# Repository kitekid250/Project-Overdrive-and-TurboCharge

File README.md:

# Project Overdrive and TurboCharge

OverDrive and TurboCharge are simple motor control modules designed for use by the Bucknell Department of Mechanical Engineering.  The boards are designed to be a simple interface with motors and encoders.  ProjectOverdrive is the big brother of Turbocharger and was develped to handle 6 high power motors (24V @ 20A ea) and have 6 encoder counters designed for an Arduino Due. Project TurboCharge is the little brother, powered from a L298P dual H-bridge, and fits nicely on top of an Arduino Uno.  It has two channels of encoder counting using the same chip as its big brother.  Its signficantly cheaper than the TurboCharge, making it the ideal candidate for projects requiring smaller motors.

###Documentation
You should read the docs corresponding to your board then follow the Installation/QuickStart instructions below

The documentation for the OverDrive Board is [here](https://github.com/kitekid250/Project-Overdrive-and-TurboCharge/blob/master/Documentation/OverDrive%20Documentation.md).

The documentation for the TurboCharge Board is [here](https://github.com/kitekid250/Project-Overdrive-and-TurboCharge/blob/master/Documentation/TurboCharge%20Documentation.md).

The (advanced) documentation for the encoder counter IC's is [here](https://github.com/kitekid250/Project-Overdrive-and-TurboCharge/blob/master/Documentation/LS7366R%20Encoder%20Counter%20Documentation.md).

###Installation/QuickStart
Here are the steps to get going, starting from square one.

1. Install Arduino 1.6.6 from [here](https://www.arduino.cc/en/Main/OldSoftwareReleases#previous).  There is a good chance that other Arduino versions will work, but this library is confirmed to work on 1.6.6.
2. Download the [OverDrive library](https://github.com/kitekid250/Project-Overdrive-and-TurboCharge/raw/master/OverDrive/OverDrive_Library.zip) if you have an OverDrive board or the [TurboCharge library](https://github.com/kitekid250/Project-Overdrive-and-TurboCharge/raw/master/TurboCharge/TurboCharge_Library.zip) if you have a TurboCharge board.  Keep them as .ZIP files so Arduino can easily import them.
3. Install the library you just downloaded by navigating to Sketch->Include Library-> Add .ZIP Library
4. In the Arduino IDE navigate to Tools->Board->Boards Manager
5. Search for "due" and install version 1.6.6 of the one board that comes up.
6. Navigate to File->Examples->[OverDrive/TurboCharge]_Library->Example->E01...
7. Connect the Arduino Due or Arduino Uno that is connected to your OverDrive or TurboCharge board respectively.  If it is a Due, make sure that you plug into the Due's Programming Port (it says it on the bottom of the board).
8. Select the correct COM port from Tools->Port->[Whichever indicates "(Arduino Due/Uno)"]
9. Select Tools->Board->[Arduino Due (Programming Port) / Arduino Uno]
10. Press the Upload (right arrow) button in the toolbar to run the example on the board.

###About
This project is currently maintained by Ward Prescott (erp006@bucknell.edu), however Phil Diefenderfer is responsible for the current hardware design and the first draft of the documentation and libraries.

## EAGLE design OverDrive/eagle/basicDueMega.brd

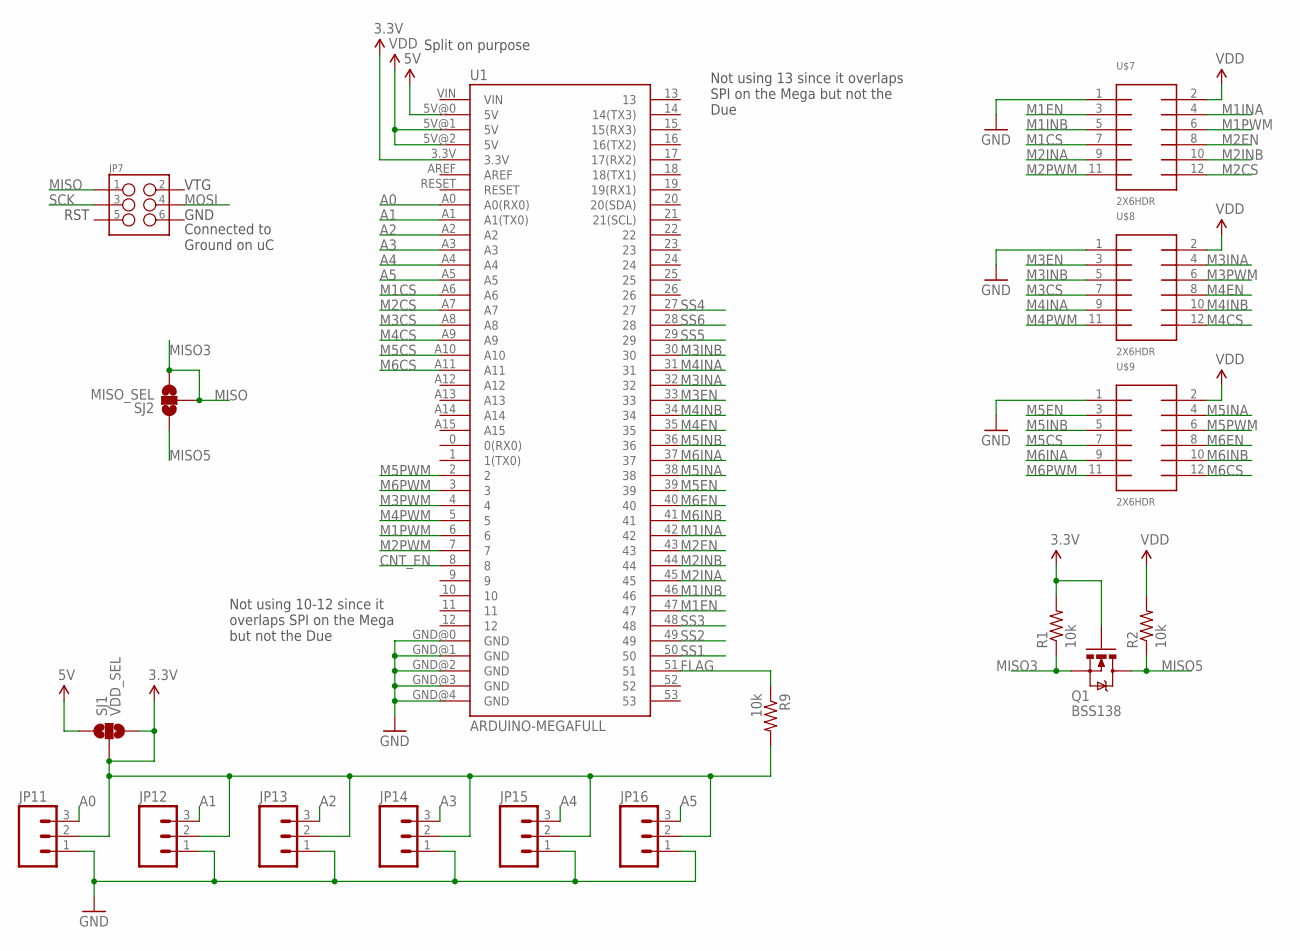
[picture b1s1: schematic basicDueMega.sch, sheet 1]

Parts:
JP7: M03X2POGO_PINS; 2X3_POGO
JP11, JP12, JP13, JP14, JP15, JP16: M03LOCK; 1X03_LOCK
Q1: MOSFET-NCHANNELBSS123LT1G; SOT23
R1, R2, R9: 10k; 0603-RES
SJ1: VDD_SEL; SJ_2
SJ2: MISO_SEL; SJ_2
U1: ARDUINO-MEGAFULL; ARDUINO_MEGA
U$7, U$8, U$9: 2X6HDR; 2X6_2MM_SHROUD

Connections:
3.3V: JP11.2, JP12.2, JP13.2, JP14.2, JP15.2, JP16.2, Q1.1 (G), R1.2, R9.2, SJ1.2, SJ1.3, U1.3.3V
5V: SJ1.1, U1.5V@0 (5V); also elsewhere on the board
A0: JP11.3, U1.A0 (A0(RX0))
A1: JP12.3, U1.A1 (A1(TX0))
A2: JP13.3, U1.A2
A3: JP14.3, U1.A3
A4: JP15.3, U1.A4
A5: JP16.3, U1.A5
CNT_EN: U1.8; also elsewhere on the board
FLAG: R9.1, U1.51; also elsewhere on the board
GND: JP11.1, JP12.1, JP13.1, JP14.1, JP15.1, JP16.1, U1.GND@0 (GND), U1.GND@1 (GND), U1.GND@2 (GND), U1.GND@3 (GND), U1.GND@4 (GND), U$7.1, U$8.1, U$9.1; also elsewhere on the board
M1CS: U1.A6, U$7.7
M1EN: U1.47, U$7.3
M1INA: U1.42, U$7.4
M1INB: U1.46, U$7.5
M1PWM: U1.6, U$7.6
M2CS: U1.A7, U$7.12
M2EN: U1.43, U$7.8
M2INA: U1.45, U$7.9
M2INB: U1.44, U$7.10
M2PWM: U1.7, U$7.11
M3CS: U1.A8, U$8.7
M3EN: U1.33, U$8.3
M3INA: U1.32, U$8.4
M3INB: U1.30, U$8.5
M3PWM: U1.4, U$8.6
M4CS: U1.A9, U$8.12
M4EN: U1.35, U$8.8
M4INA: U1.31, U$8.9
M4INB: U1.34, U$8.10
M4PWM: U1.5, U$8.11
M5CS: U1.A10, U$9.7
M5EN: U1.39, U$9.3
M5INA: U1.38, U$9.4
M5INB: U1.36, U$9.5
M5PWM: U1.2, U$9.6
M6CS: U1.A11, U$9.12
M6EN: U1.40, U$9.8
M6INA: U1.37, U$9.9
M6INB: U1.41, U$9.10
M6PWM: U1.3, U$9.11
MISO3: JP7.P$1 (1), Q1.2 (S), R1.1, SJ2.2, SJ2.3
MISO5: Q1.3 (D), R2.1, SJ2.1; also elsewhere on the board
MOSI: JP7.P$4 (4); also elsewhere on the board
SCK: JP7.P$3 (3); also elsewhere on the board
SS1: U1.50; also elsewhere on the board
SS2: U1.49; also elsewhere on the board
SS3: U1.48; also elsewhere on the board
SS4: U1.27; also elsewhere on the board
SS5: U1.29; also elsewhere on the board
SS6: U1.28; also elsewhere on the board
VDD: R2.2, U1.5V@1 (5V), U1.5V@2 (5V), U$7.2, U$8.2, U$9.2

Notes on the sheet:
BSS138
Connected to Ground on uC
VTG
Not using 13 since it overlaps SPI on the Mega but not the Due
Not using 10-12 since it overlaps SPI on the Mega but not the Due
MISO
RST
GND
Split on purpose

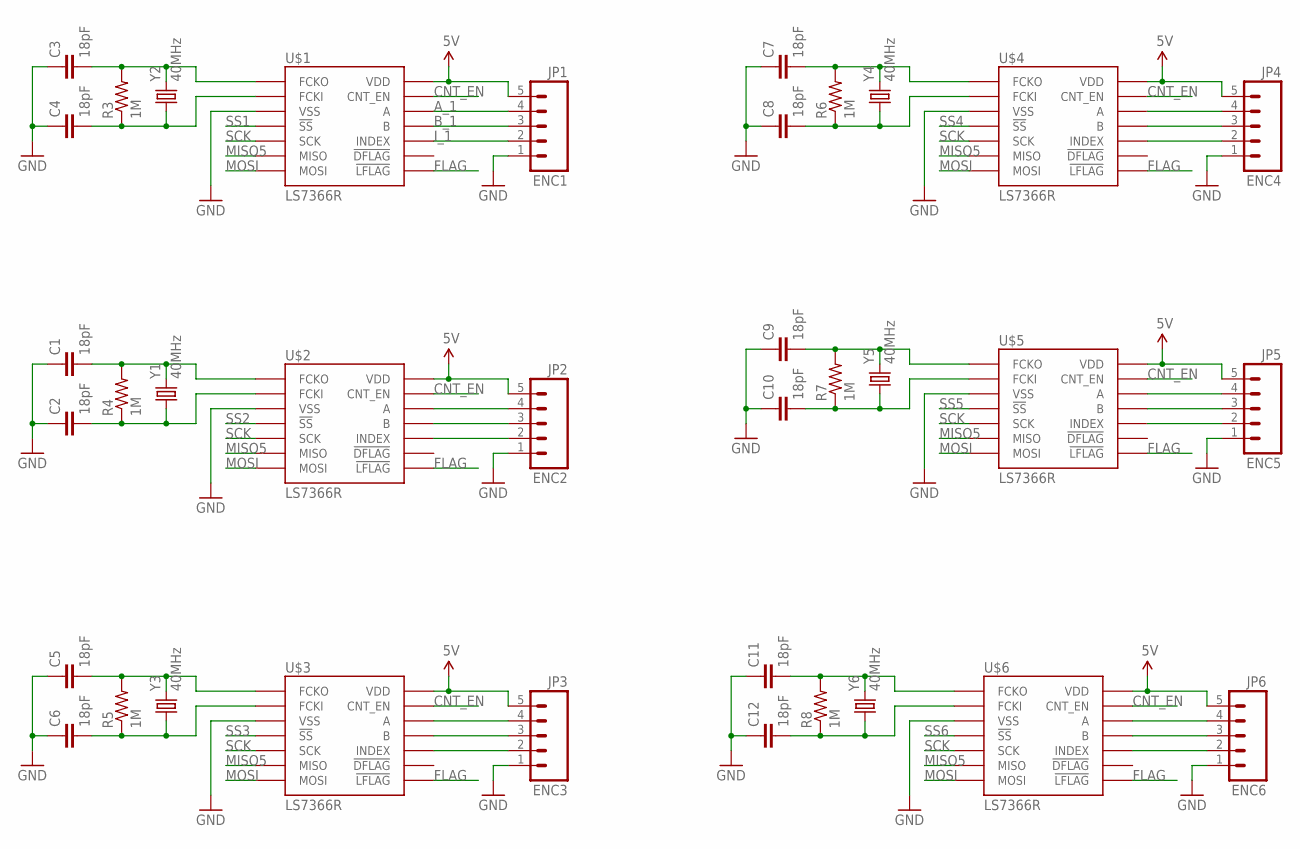
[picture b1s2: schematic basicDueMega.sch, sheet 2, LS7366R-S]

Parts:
C1, C2, C3, C4, C5, C6, C7, C8, C9, C10, C11, C12: 18pF; 0603-CAP
JP1: ENC1; 1X05_LOCK
JP2: ENC2; 1X05_LOCK
JP3: ENC3; 1X05_LOCK
JP4: ENC4; 1X05_LOCK
JP5: ENC5; 1X05_LOCK
JP6: ENC6; 1X05_LOCK
R3, R4, R5, R6, R7, R8: 1M; 0603-RES
U$1, U$2, U$3, U$4, U$5, U$6: LS7366R; SOIC14
Y1, Y2, Y3, Y4, Y5, Y6: 40MHz; CRYSTAL-SMD-5X3

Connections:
5V: JP1.5, JP2.5, JP3.5, JP4.5, JP5.5, JP6.5, U$1.14 (VDD), U$2.14 (VDD), U$3.14 (VDD), U$4.14 (VDD), U$5.14 (VDD), U$6.14 (VDD); also elsewhere on the board
A_1: JP1.4, U$1.12 (A)
B_1: JP1.3, U$1.11 (B)
CNT_EN: U$1.13 (CNT_EN), U$2.13 (CNT_EN), U$3.13 (CNT_EN), U$4.13 (CNT_EN), U$5.13 (CNT_EN), U$6.13 (CNT_EN); also elsewhere on the board
FLAG: U$1.8 (!LFLAG), U$2.8 (!LFLAG), U$3.8 (!LFLAG), U$4.8 (!LFLAG), U$5.8 (!LFLAG), U$6.8 (!LFLAG); also elsewhere on the board
GND: C1.1, C2.1, C3.1, C4.1, C5.1, C6.1, C7.1, C8.1, C9.1, C10.1, C11.1, C12.1, JP1.1, JP2.1, JP3.1, JP4.1, JP5.1, JP6.1, U$1.3 (VSS), U$2.3 (VSS), U$3.3 (VSS), U$4.3 (VSS), U$5.3 (VSS), U$6.3 (VSS); also elsewhere on the board
I_1: JP1.2, U$1.10 (INDEX)
MISO5: U$1.6 (MISO), U$2.6 (MISO), U$3.6 (MISO), U$4.6 (MISO), U$5.6 (MISO), U$6.6 (MISO); also elsewhere on the board
MOSI: U$1.7 (MOSI), U$2.7 (MOSI), U$3.7 (MOSI), U$4.7 (MOSI), U$5.7 (MOSI), U$6.7 (MOSI); also elsewhere on the board
unnamed: C3.2, R3.2, U$1.1 (FCKO), Y2.3 (2)
unnamed: C4.2, R3.1, U$1.2 (FCKI), Y2.1
unnamed: JP2.4, U$2.12 (A)
unnamed: JP2.3, U$2.11 (B)
unnamed: JP2.2, U$2.10 (INDEX)
unnamed: C1.2, R4.2, U$2.1 (FCKO), Y1.3 (2)
unnamed: C2.2, R4.1, U$2.2 (FCKI), Y1.1
unnamed: JP3.4, U$3.12 (A)
unnamed: JP3.3, U$3.11 (B)
unnamed: JP3.2, U$3.10 (INDEX)
unnamed: C5.2, R5.2, U$3.1 (FCKO), Y3.3 (2)
unnamed: C6.2, R5.1, U$3.2 (FCKI), Y3.1
unnamed: JP4.4, U$4.12 (A)
unnamed: JP4.3, U$4.11 (B)
unnamed: JP4.2, U$4.10 (INDEX)
unnamed: C7.2, R6.2, U$4.1 (FCKO), Y4.3 (2)
unnamed: C8.2, R6.1, U$4.2 (FCKI), Y4.1
unnamed: JP5.4, U$5.12 (A)
unnamed: JP5.3, U$5.11 (B)
unnamed: JP5.2, U$5.10 (INDEX)
unnamed: C9.2, R7.2, U$5.1 (FCKO), Y5.3 (2)
unnamed: C10.2, R7.1, U$5.2 (FCKI), Y5.1
unnamed: JP6.4, U$6.12 (A)
unnamed: JP6.3, U$6.11 (B)
unnamed: JP6.2, U$6.10 (INDEX)
unnamed: C11.2, R8.2, U$6.1 (FCKO), Y6.3 (2)
unnamed: C12.2, R8.1, U$6.2 (FCKI), Y6.1
SCK: U$1.5 (SCK), U$2.5 (SCK), U$3.5 (SCK), U$4.5 (SCK), U$5.5 (SCK), U$6.5 (SCK); also elsewhere on the board
SS1: U$1.4 (!SS); also elsewhere on the board
SS2: U$2.4 (!SS); also elsewhere on the board
SS3: U$3.4 (!SS); also elsewhere on the board
SS4: U$4.4 (!SS); also elsewhere on the board
SS5: U$5.4 (!SS); also elsewhere on the board
SS6: U$6.4 (!SS); also elsewhere on the board

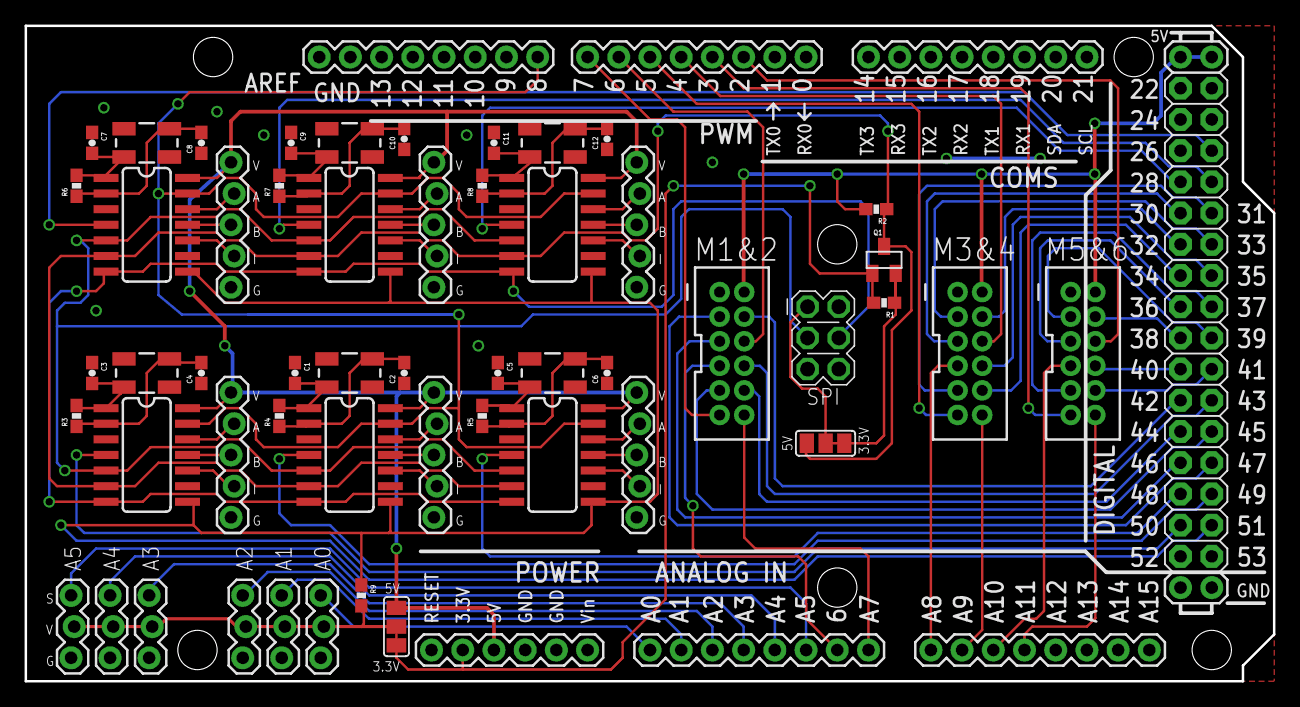
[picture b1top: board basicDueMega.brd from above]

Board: 2 copper layers, 101.6 x 53.3 mm, 53 parts (0 on the bottom side), 82 nets.

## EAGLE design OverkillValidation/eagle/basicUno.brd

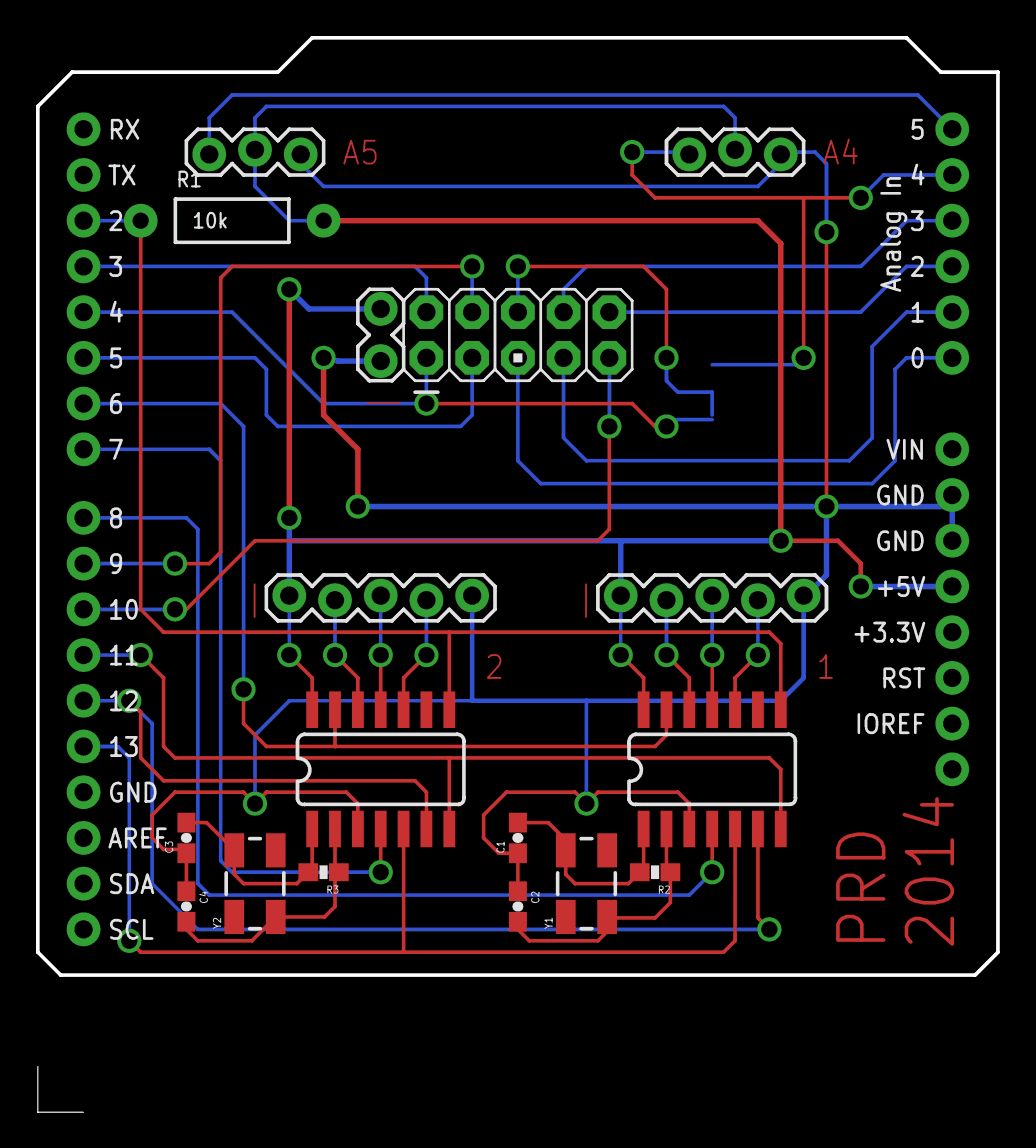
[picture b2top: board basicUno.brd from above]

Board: 2 copper layers, 53.3 x 59.6 mm, 19 parts (1 on the bottom side), 31 nets.

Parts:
C1, C2, C3, C4: 18pF; 0603-CAP
JP1: EN1; 1X05_LOCK
JP2: EN2; 1X05_LOCK
JP3: M05X2PTH; AVR_ICSP
JP4: M02LOCK; 1X02_LOCK
JP5: A4; 1X03_LOCK
JP6: A5; 1X03_LOCK
R1: 10k; AXIAL-0.4
R2, R3: 1M; 0603-RES
SJ1: SJ_2
U$1, U$2: LS7366R; SOIC14
U$3: ARDUINO_R3_SHIELD; UNO_R3_SHIELD
Y1, Y2: 40MHz; CRYSTAL-SMD-5X3

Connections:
5V: JP1.1, JP2.1, JP4.1, JP5.2, JP6.2, R1.P$2, U$1.14, U$2.14, U$3.5V
!FLAG: R1.P$1, U$1.8, U$2.8, U$3.D2
!SS1: U$1.4, U$3.D8
!SS2: U$2.4, U$3.D7
A4: JP5.3, SJ1.3, U$3.A4
A5: JP6.3, U$3.A5
CNT_EN: U$1.13, U$2.13, U$3.D6
GND: C1.1, C2.1, C3.1, C4.1, JP1.5, JP2.5, JP4.2, JP5.1, JP6.1, U$1.3, U$2.3, U$3.GND@0, U$3.GND@1
M1CS: JP3.5, U$3.A0
M1EN: JP3.1, SJ1.1, U$3.D4
M1INA: JP3.2, U$3.D3
M1INB: JP3.3, U$3.D5
M1PWM: JP3.4, U$3.D9
M2CS: JP3.10, U$3.A2
M2EN: JP3.6, SJ1.2
M2INA: JP3.7, U$3.A1
M2INB: JP3.8, U$3.A3
M2PWM: JP3.9, U$3.D10
MISO: U$1.6, U$2.6, U$3.D12
MOSI: U$1.7, U$2.7, U$3.D11
unnamed: JP1.2, U$1.12
unnamed: JP1.3, U$1.11
unnamed: JP1.4, U$1.10
unnamed: JP2.2, U$2.12
unnamed: JP2.3, U$2.11
unnamed: JP2.4, U$2.10
unnamed: C1.2, R2.2, U$1.1, Y1.3
unnamed: C2.2, R2.1, U$1.2, Y1.1
unnamed: C3.2, R3.2, U$2.1, Y2.3
unnamed: C4.2, R3.1, U$2.2, Y2.1
SCK: U$1.5, U$2.5, U$3.D13

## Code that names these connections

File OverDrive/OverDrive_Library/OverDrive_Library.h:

#ifndef _OVERDRIVE_BASIC
#define _OVERDRIVE_BASIC

// Encoder Interface Pins
#define ENC1 50
#define ENC2 49
#define ENC3 48
#define ENC4 27
#define ENC5 29
#define ENC6 28
#define CNT_EN 8
#define FLAG 51
// +SPI on ICSP header

// Driver Interface Pins
#define M1CS A6
#define M2CS A7
#define M3CS A8
#define M4CS A9
#define M5CS A10
#define M6CS A11

#define M1PWM 6
#define M2PWM 7
#define M3PWM 4
#define M4PWM 5
#define M5PWM 2
#define M6PWM 3

#define M1EN 47
#define M1INA 42
#define M1INB 46

#define M2EN 43
#define M2INA 45
#define M2INB 44

#define M3EN 33
#define M3INA 32
#define M3INB 30

#define M4EN 35
#define M4INA 31
#define M4INB 34

#define M5EN 39
#define M5INA 38
#define M5INB 36

#define M6EN 40
#define M6INA 37
#define M6INB 41

// Constants
#define ENABLED 1
#define DISABLED 0
#define FORWARD 0
#define BACKWARD 1

#define MOTOR1 1
#define MOTOR2 2
#define MOTOR3 3
#define MOTOR4 4
#define MOTOR5 5
#define MOTOR6 6

class OverDriveBasic
{
  public:
    OverDriveBasic(int motorNum); 
    void setDirection(int dir);
    void setEnable(int en);
    void setPWM(int spd);
    int getCurrent();
   private:
     int _MOTOR;
     int _EN;
     int _INA;
     int _INB;
     int _PWM;
     int _CS;
};

#endif /* _OVERDRIVE_BASIC */

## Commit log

2015-03-16 Actual first Commit of Files being migrated
    First Commit of Files being migrated from Google Code to GitHub
2015-06-02 Updated Pin Definitions for Production Revision
    The pin defs in the header changed quite a bit.
2015-06-03 Fixed the issue with the SPI library and Arduino Due misbehaving in the LS7366R library. Issue was where SPI.begin() was in the constructor which caused the Due to lock up. This works in the Uno but 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
2015-06-03 Removed OverDriveTesting in the code folder. It is old and really should not be used or present.
2015-06-09 Added Suggestions Text File
    This could serve as a repository for our thoughts on this project, and a
    psuedo To-Do list. We could incorporate git issues as well if desired.
2015-06-09 Added Example and Fixed a Pin
    The example works with the due and a motor. The pin mis-mapped was
    M1_INA.
2015-06-25 Added Set Counter Functionality
    It works, though the user has to make sure not to pass a number that
    exceeds the byte length the counter register is set to.
2015-10-17 Added LS User Guide PDF
    It was only in the Turbo repo though it applies to both Turbo Charge and
    OverDrive
2015-11-09 Started Merge of Two Repos, Started Markdown Documentation
    Moving towards the eventual goal of cross platform documentation, and a
    unified repo for all the libraries.
2015-11-09 Updated Readme.md
    It now reflects the status of the current repo and the project as a
    whole.
2015-11-10 Started TurboCharger Documentation
2015-11-18 Added Diagram
2015-11-18 TurboCharger Documentation R1
    I think I just about got the rough draft done. Further additions and
    edits will be necessary in due time.
2015-11-20 Added More Examples
    With potentiometers!
2015-12-05 Removed Space in Example Title
2015-12-22 Big Reorg, Started Unification
    My end goal is to have single libraries for both boards that tie
    everything together. Progress was made toward this with reorg though
    the unified libraries are currently not tested as stable.
2015-12-22 Finished OverDrive Example 1, Started 2 and 3
    I have to try them on the real boards, but I like the direction they're
    heading. Quite easy to use!
2015-12-22 Remembered to update the ZIP library
    Just in case anyone wants to use this right now.
2015-12-23 OverDrive Example 2 and 3 Completed
    I didn't do much to 3, but it's more about the comments anyway.
2015-12-23 Updated the ZIP too
2015-12-23 Reorg Documentation
2015-12-23 New Readme
    Added installation instructions, whohoo!
2015-12-23 Bleh
2015-12-23 Made an OverDrive User Guide, More Reorg
    Woohoo, all done for now.

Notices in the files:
parts and their libraries:
SparkFun-Boards: Licensing: Creative Commons ShareAlike 4.0 International - https://creativecommons.org/licenses/by-sa/4.0
